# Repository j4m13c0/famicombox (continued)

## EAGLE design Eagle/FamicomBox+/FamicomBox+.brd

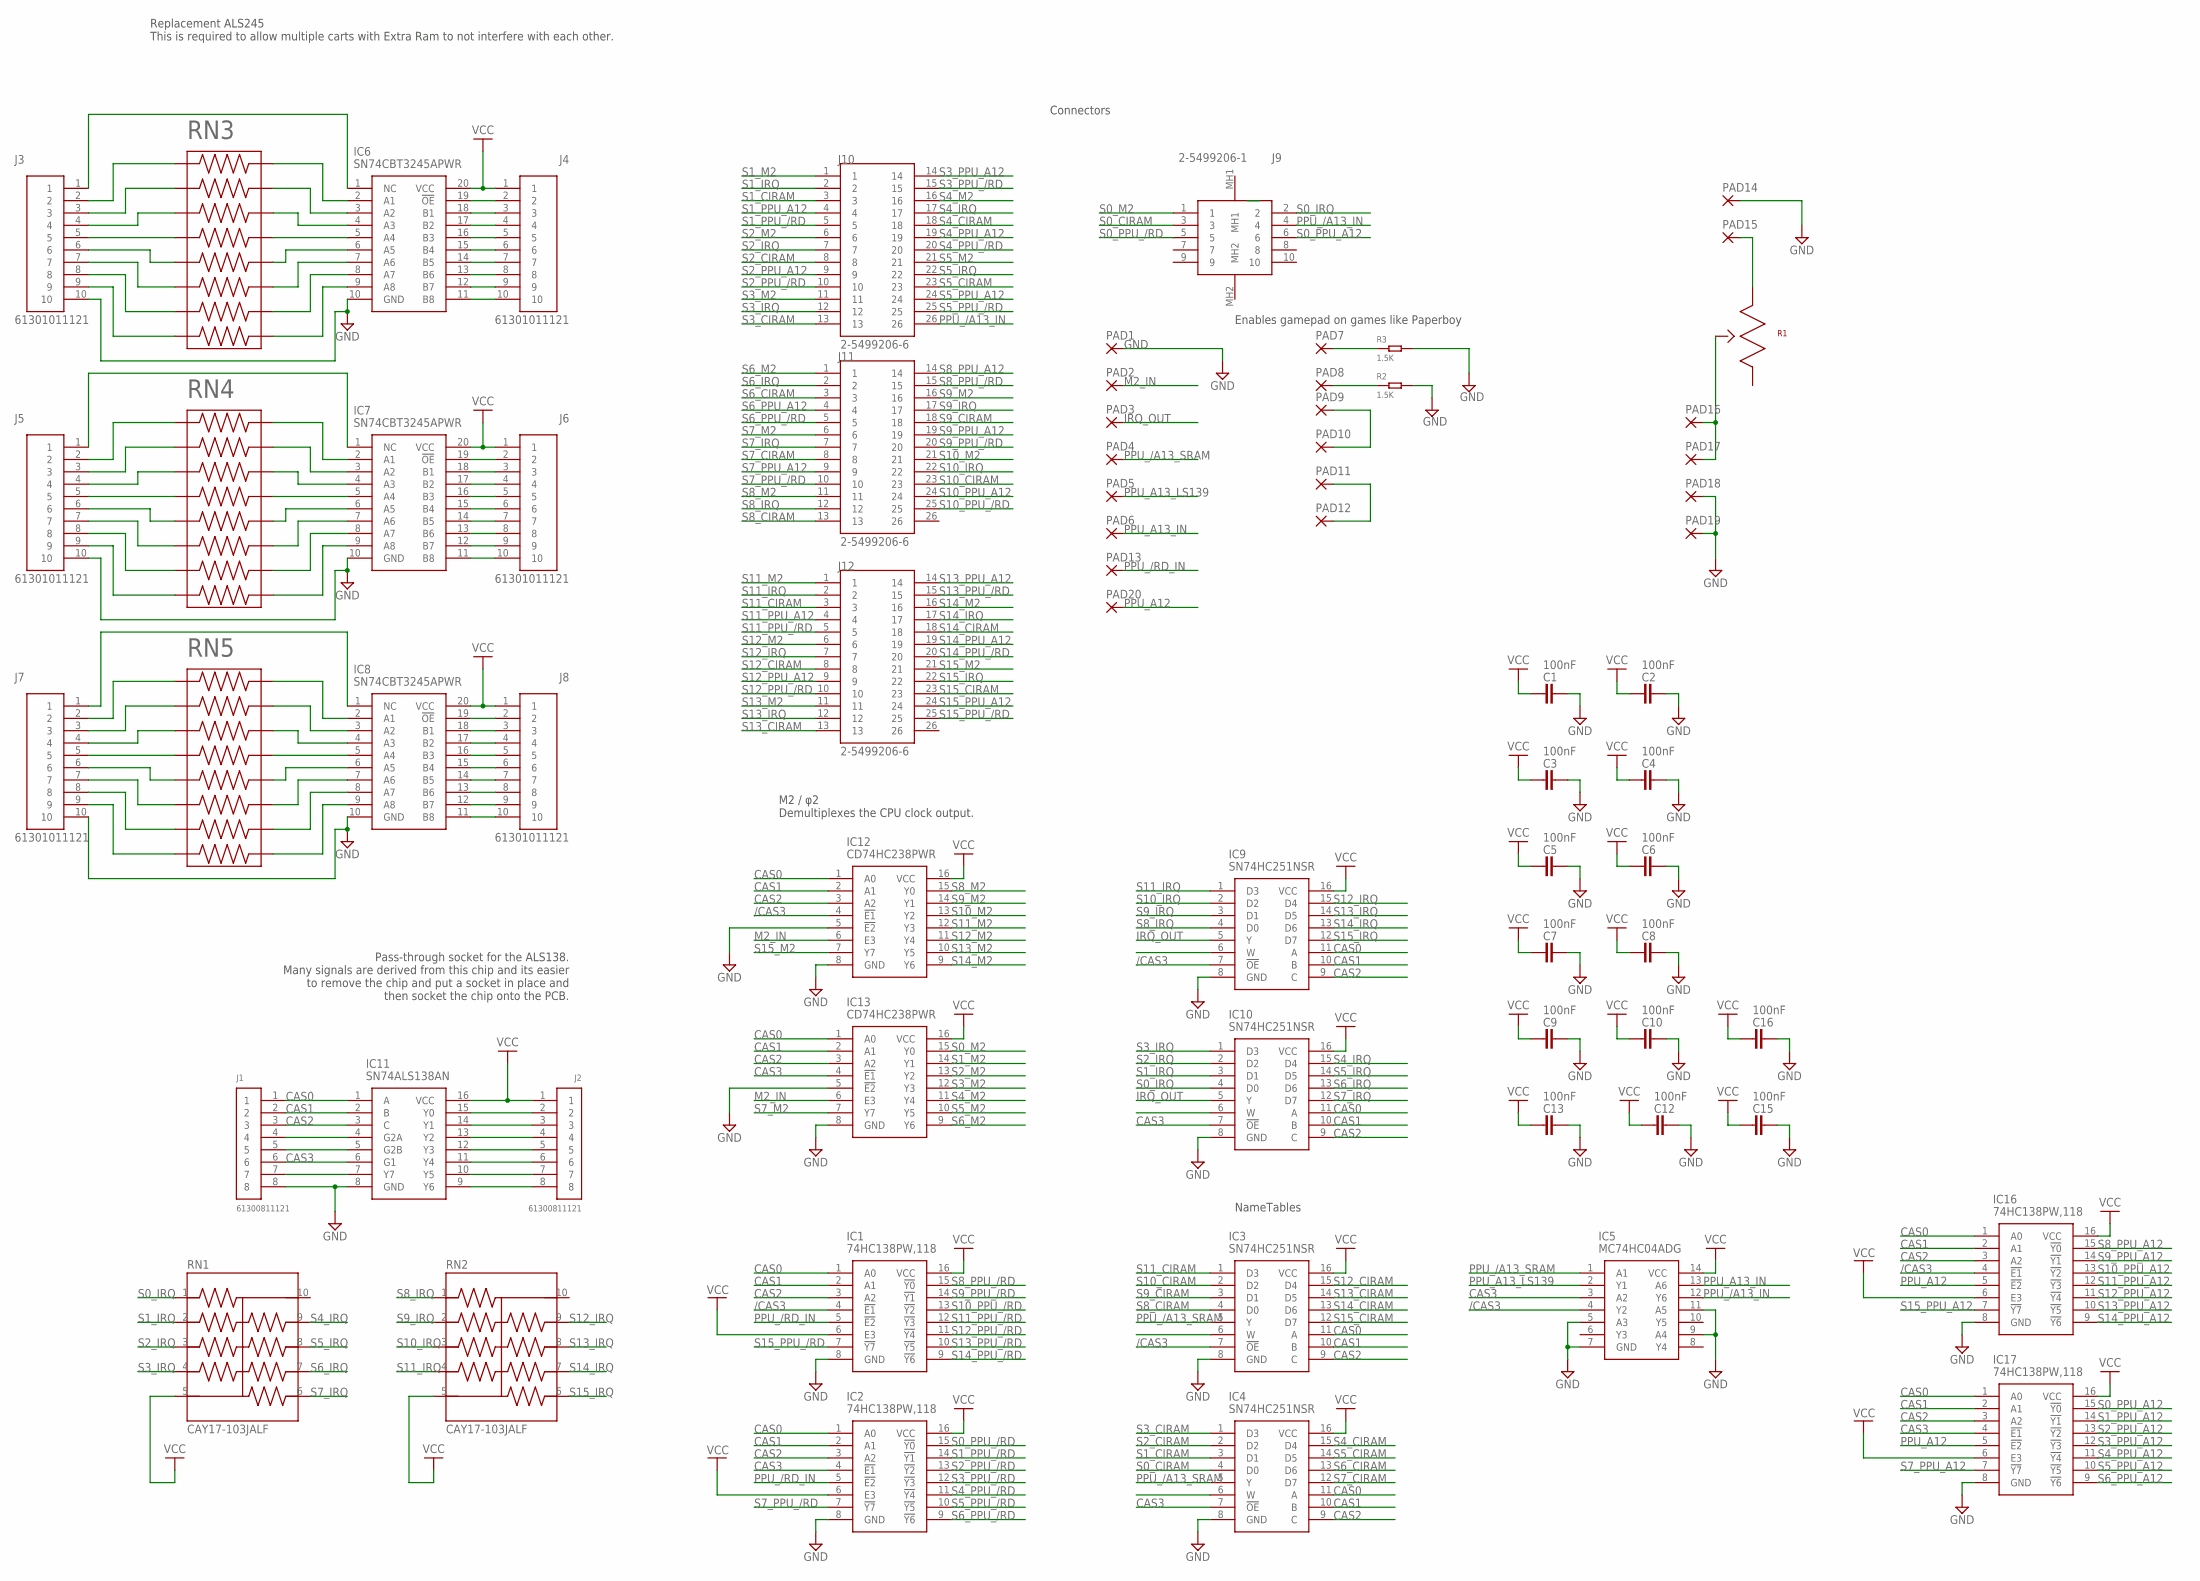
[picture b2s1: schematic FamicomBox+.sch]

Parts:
C1, C2, C3, C4, C5, C6, C7, C8, C9, C10, C12, C13, C15, C16: 100nF; CAPC1608X85
IC1, IC2, IC16, IC17: 74HC138PW,118; SOP65P640X110-16N
IC3, IC4, IC9, IC10: SN74HC251NSR; SOIC127P780X200-16N
IC5: MC74HC04ADG; SOIC127P600X175-14N
IC6, IC7, IC8: SN74CBT3245APWR; SOP65P640X120-20N
IC11: SN74ALS138AN; DIP254P762X508-16
IC12, IC13: CD74HC238PWR; SOP65P640X120-16N
J1, J2: 61300811121
J3, J4, J5, J6, J7, J8: 61301011121
J9: 2-5499206-1; 254992061
J10, J11, J12: 2-5499206-6; TE_2-5499206-6
PAD1, PAD2, PAD3, PAD4, PAD5, PAD6, PAD7, PAD8, PAD9, PAD10, PAD11, PAD12, PAD13, PAD14, PAD15, PAD16, PAD17, PAD18, PAD19, PAD20: WIREPAD2,54/1,0; 2,54/1,0
R1: PTV09A-4020F-A504; PTV09
R2, R3: 1.5K; R0603
RN1, RN2: CAY17-103JALF; RESCAXS64P320X160X60-10N
RN3, RN4, RN5: 4816P-1-562LF; SOIC127P762X240-16N

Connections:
/CAS3: IC1.4 (!E1), IC3.7 (!OE), IC5.4 (Y2), IC9.7 (!OE), IC12.4 (!E1), IC16.4 (!E1)
CAS0: IC1.1 (A0), IC2.1 (A0), IC3.11 (A), IC4.11 (A), IC9.11 (A), IC10.11 (A), IC11.1 (A), IC12.1 (A0), IC13.1 (A0), IC16.1 (A0), IC17.1 (A0), J1.1
CAS1: IC1.2 (A1), IC2.2 (A1), IC3.10 (B), IC4.10 (B), IC9.10 (B), IC10.10 (B), IC11.2 (B), IC12.2 (A1), IC13.2 (A1), IC16.2 (A1), IC17.2 (A1), J1.2
CAS2: IC1.3 (A2), IC2.3 (A2), IC3.9 (C), IC4.9 (C), IC9.9 (C), IC10.9 (C), IC11.3 (C), IC12.3 (A2), IC13.3 (A2), IC16.3 (A2), IC17.3 (A2), J1.3
CAS3: IC2.4 (!E1), IC4.7 (!OE), IC5.3 (A2), IC10.7 (!OE), IC11.6 (G1), IC13.4 (!E1), IC17.4 (!E1), J1.6
GND: C1.1, C2.1, C3.1, C4.1, C5.1, C6.1, C7.1, C8.1, C9.1, C10.1, C12.1, C13.1, C15.1, C16.1, IC1.8 (GND), IC2.8 (GND), IC3.8 (GND), IC4.8 (GND), IC5.5 (A3), IC5.7 (GND), IC5.9 (A4), IC5.11 (A5), IC6.10 (GND), IC7.10 (GND), IC8.10 (GND), IC9.8 (GND), IC10.8 (GND), IC11.8 (GND), IC12.5 (!E2), IC12.8 (GND), IC13.5 (!E2), IC13.8 (GND), IC16.8 (GND), IC17.8 (GND), J1.8, J3.10, J5.10, J7.10, PAD1.1, PAD14.1, PAD18.1, PAD19.1, R2.2, R3.2
IRQ_OUT: IC9.5 (Y), IC10.5 (Y), PAD3.1
M2_IN: IC12.6 (E3), IC13.6 (E3), PAD2.1
unnamed: IC6.2 (A1), RN3.16
unnamed: IC6.3 (A2), RN3.15
unnamed: IC6.4 (A3), RN3.14
unnamed: IC6.5 (A4), RN3.13
unnamed: IC6.6 (A5), RN3.12
unnamed: IC6.7 (A6), RN3.11
unnamed: IC6.8 (A7), RN3.10
unnamed: IC6.9 (A8), RN3.9
unnamed: J3.2, RN3.1
unnamed: J3.3, RN3.2
unnamed: IC6.11 (B8), J4.10
unnamed: IC6.12 (B7), J4.9
unnamed: IC6.13 (B6), J4.8
unnamed: IC6.14 (B5), J4.7
unnamed: IC6.15 (B4), J4.6
unnamed: IC6.16 (B3), J4.5
unnamed: IC6.17 (B2), J4.4
unnamed: IC6.18 (B1), J4.3
unnamed: IC6.19 (!OE), J4.2
unnamed: J3.4, RN3.3
unnamed: J3.5, RN3.4
unnamed: J3.6, RN3.5
unnamed: J3.7, RN3.6
unnamed: J3.8, RN3.7
unnamed: J3.9, RN3.8
unnamed: IC6.1 (NC), J3.1
unnamed: J7.2, RN5.1
unnamed: IC7.11 (B8), J6.10
unnamed: IC7.12 (B7), J6.9
unnamed: IC7.13 (B6), J6.8
unnamed: IC7.14 (B5), J6.7
unnamed: IC7.15 (B4), J6.6
unnamed: IC7.16 (B3), J6.5
unnamed: IC7.17 (B2), J6.4
unnamed: IC7.18 (B1), J6.3
unnamed: IC7.19 (!OE), J6.2
unnamed: IC8.19 (!OE), J8.2
unnamed: IC8.18 (B1), J8.3
unnamed: IC8.17 (B2), J8.4
unnamed: IC8.16 (B3), J8.5
unnamed: IC8.15 (B4), J8.6
unnamed: IC8.14 (B5), J8.7
unnamed: IC8.13 (B6), J8.8
unnamed: IC8.12 (B7), J8.9
unnamed: IC8.11 (B8), J8.10
unnamed: IC7.5 (A4), RN4.13
unnamed: J5.5, RN4.4
unnamed: J5.2, RN4.1
unnamed: J5.3, RN4.2
unnamed: J5.4, RN4.3
unnamed: J5.6, RN4.5
unnamed: J5.7, RN4.6
unnamed: J5.8, RN4.7
unnamed: J5.9, RN4.8
unnamed: IC11.15 (Y0), J2.2
unnamed: IC11.14 (Y1), J2.3
unnamed: IC11.13 (Y2), J2.4
unnamed: IC11.12 (Y3), J2.5
unnamed: IC11.11 (Y4), J2.6
unnamed: IC11.10 (Y5), J2.7
unnamed: IC11.9 (Y6), J2.8
unnamed: IC11.4 (G2A), J1.4
unnamed: PAD9.1, PAD10.1
unnamed: PAD11.1, PAD12.1
unnamed: IC7.4 (A3), RN4.14
unnamed: IC11.5 (G2B), J1.5
unnamed: IC7.3 (A2), RN4.15
unnamed: IC11.7 (Y7), J1.7
unnamed: IC7.2 (A1), RN4.16
unnamed: IC7.1 (NC), J5.1
unnamed: IC7.6 (A5), RN4.12
unnamed: IC7.7 (A6), RN4.11
unnamed: IC7.8 (A7), RN4.10
unnamed: IC7.9 (A8), RN4.9
unnamed: J7.3, RN5.2
unnamed: J7.5, RN5.4
unnamed: IC8.5 (A4), RN5.13
unnamed: IC8.4 (A3), RN5.14
unnamed: IC8.3 (A2), RN5.15
unnamed: IC8.2 (A1), RN5.16
unnamed: IC8.6 (A5), RN5.12
unnamed: IC8.7 (A6), RN5.11
unnamed: IC8.8 (A7), RN5.10
unnamed: IC8.9 (A8), RN5.9
unnamed: IC8.1 (NC), J7.1
unnamed: J7.4, RN5.3
unnamed: J7.6, RN5.5
unnamed: J7.7, RN5.6
unnamed: J7.8, RN5.7
unnamed: J7.9, RN5.8
unnamed: PAD15.1, R1.1
unnamed: PAD16.1, PAD17.1, R1.2
unnamed: PAD8.1, R2.1
unnamed: PAD7.1, R3.1
PPU_/A13_IN: IC5.12 (Y6), J9.4, J10.26
PPU_/A13_SRAM: IC3.5 (Y), IC4.5 (Y), IC5.1 (A1), PAD4.1
PPU_/RD_IN: IC1.5 (!E2), IC2.5 (!E2), PAD13.1
PPU_A12: IC16.5 (!E2), IC17.5 (!E2), PAD20.1
PPU_A13_IN: IC5.13 (A6), PAD6.1
PPU_A13_LS139: IC5.2 (Y1), PAD5.1
S0_CIRAM: IC4.4 (D0), J9.3
S0_IRQ: IC10.4 (D0), J9.2, RN1.1
S0_M2: IC13.15 (Y0), J9.1
S0_PPU_/RD: IC2.15 (!Y0), J9.5
S0_PPU_A12: IC17.15 (!Y0), J9.6
S1_CIRAM: IC4.3 (D1), J10.3
S1_IRQ: IC10.3 (D1), J10.2, RN1.2
S1_M2: IC13.14 (Y1), J10.1
S1_PPU_/RD: IC2.14 (!Y1), J10.5
S1_PPU_A12: IC17.14 (!Y1), J10.4
S2_CIRAM: IC4.2 (D2), J10.8
S2_IRQ: IC10.2 (D2), J10.7, RN1.3
S2_M2: IC13.13 (Y2), J10.6
S2_PPU_/RD: IC2.13 (!Y2), J10.10
S2_PPU_A12: IC17.13 (!Y2), J10.9
S3_CIRAM: IC4.1 (D3), J10.13
S3_IRQ: IC10.1 (D3), J10.12, RN1.4
S3_M2: IC13.12 (Y3), J10.11
S3_PPU_/RD: IC2.12 (!Y3), J10.15
S3_PPU_A12: IC17.12 (!Y3), J10.14
S4_CIRAM: IC4.15 (D4), J10.18
S4_IRQ: IC10.15 (D4), J10.17, RN1.9
S4_M2: IC13.11 (Y4), J10.16
S4_PPU_/RD: IC2.11 (!Y4), J10.20
S4_PPU_A12: IC17.11 (!Y4), J10.19
S5_CIRAM: IC4.14 (D5), J10.23
S5_IRQ: IC10.14 (D5), J10.22, RN1.8
S5_M2: IC13.10 (Y5), J10.21
S5_PPU_/RD: IC2.10 (!Y5), J10.25
S5_PPU_A12: IC17.10 (!Y5), J10.24
S6_CIRAM: IC4.13 (D6), J11.3
S6_IRQ: IC10.13 (D6), J11.2, RN1.7
S6_M2: IC13.9 (Y6), J11.1
S6_PPU_/RD: IC2.9 (!Y6), J11.5
S6_PPU_A12: IC17.9 (!Y6), J11.4
S7_CIRAM: IC4.12 (D7), J11.8
S7_IRQ: IC10.12 (D7), J11.7, RN1.6
S7_M2: IC13.7 (Y7), J11.6
S7_PPU_/RD: IC2.7 (!Y7), J11.10
S7_PPU_A12: IC17.7 (!Y7), J11.9
S8_CIRAM: IC3.4 (D0), J11.13
S8_IRQ: IC9.4 (D0), J11.12, RN2.1
S8_M2: IC12.15 (Y0), J11.11
S8_PPU_/RD: IC1.15 (!Y0), J11.15
S8_PPU_A12: IC16.15 (!Y0), J11.14
S9_CIRAM: IC3.3 (D1), J11.18
S9_IRQ: IC9.3 (D1), J11.17, RN2.2
S9_M2: IC12.14 (Y1), J11.16
S9_PPU_/RD: IC1.14 (!Y1), J11.20
S9_PPU_A12: IC16.14 (!Y1), J11.19
S10_CIRAM: IC3.2 (D2), J11.23
S10_IRQ: IC9.2 (D2), J11.22, RN2.3
S10_M2: IC12.13 (Y2), J11.21
S10_PPU_/RD: IC1.13 (!Y2), J11.25
S10_PPU_A12: IC16.13 (!Y2), J11.24
S11_CIRAM: IC3.1 (D3), J12.3
S11_IRQ: IC9.1 (D3), J12.2, RN2.4
S11_M2: IC12.12 (Y3), J12.1
S11_PPU_/RD: IC1.12 (!Y3), J12.5
S11_PPU_A12: IC16.12 (!Y3), J12.4
S12_CIRAM: IC3.15 (D4), J12.8
S12_IRQ: IC9.15 (D4), J12.7, RN2.9
S12_M2: IC12.11 (Y4), J12.6
S12_PPU_/RD: IC1.11 (!Y4), J12.10
S12_PPU_A12: IC16.11 (!Y4), J12.9
S13_CIRAM: IC3.14 (D5), J12.13
S13_IRQ: IC9.14 (D5), J12.12, RN2.8
S13_M2: IC12.10 (Y5), J12.11
S13_PPU_/RD: IC1.10 (!Y5), J12.15
S13_PPU_A12: IC16.10 (!Y5), J12.14
S14_CIRAM: IC3.13 (D6), J12.18
S14_IRQ: IC9.13 (D6), J12.17, RN2.7
S14_M2: IC12.9 (Y6), J12.16
S14_PPU_/RD: IC1.9 (!Y6), J12.20
S14_PPU_A12: IC16.9 (!Y6), J12.19
S15_CIRAM: IC3.12 (D7), J12.23
S15_IRQ: IC9.12 (D7), J12.22, RN2.6
S15_M2: IC12.7 (Y7), J12.21
S15_PPU_/RD: IC1.7 (!Y7), J12.25
S15_PPU_A12: IC16.7 (!Y7), J12.24
VCC: C1.2, C2.2, C3.2, C4.2, C5.2, C6.2, C7.2, C8.2, C9.2, C10.2, C12.2, C13.2, C15.2, C16.2, IC1.6 (E3), IC1.16 (VCC), IC2.6 (E3), IC2.16 (VCC), IC3.16 (VCC), IC4.16 (VCC), IC5.14 (VCC), IC6.20 (VCC), IC7.20 (VCC), IC8.20 (VCC), IC9.16 (VCC), IC10.16 (VCC), IC11.16 (VCC), IC12.16 (VCC), IC13.16 (VCC), IC16.6 (E3), IC16.16 (VCC), IC17.6 (E3), IC17.16 (VCC), J2.1, J4.1, J6.1, J8.1, RN1.5, RN2.5

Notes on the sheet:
Replacement ALS245 This is required to allow multiple carts with Extra Ram to not interfere with each other.
Pass-through socket for the ALS138. Many signals are derived from this chip and its easier to remove the chip and put a socket in place and then socket the chip onto the PCB.
Connectors
M2 / φ2 Demultiplexes the CPU clock output.
Enables gamepad on games like Paperboy
NameTables

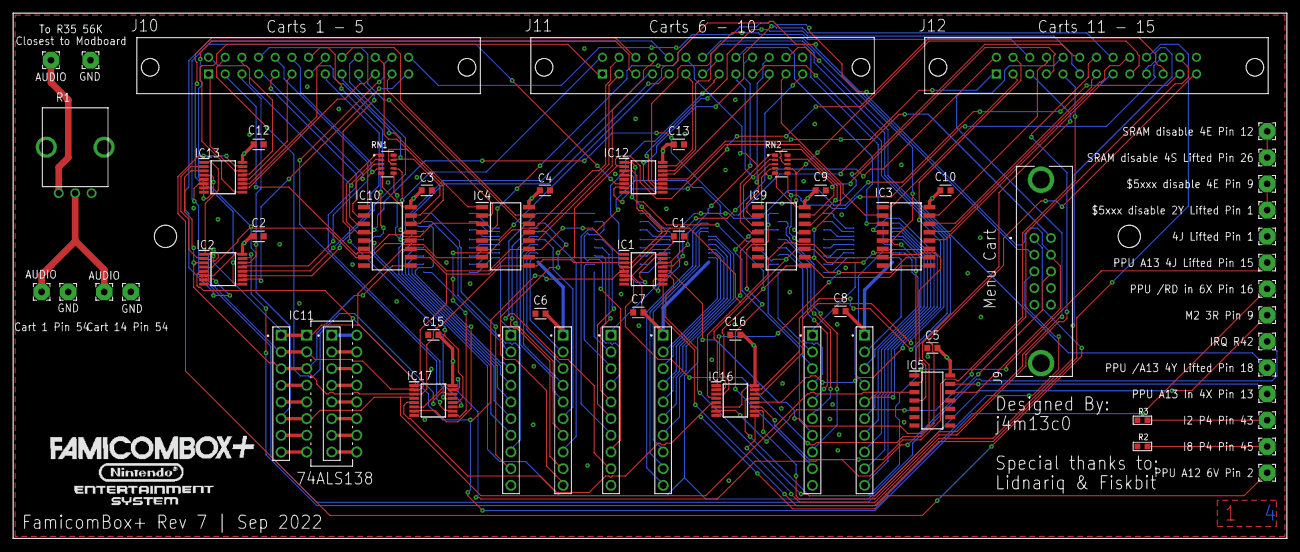
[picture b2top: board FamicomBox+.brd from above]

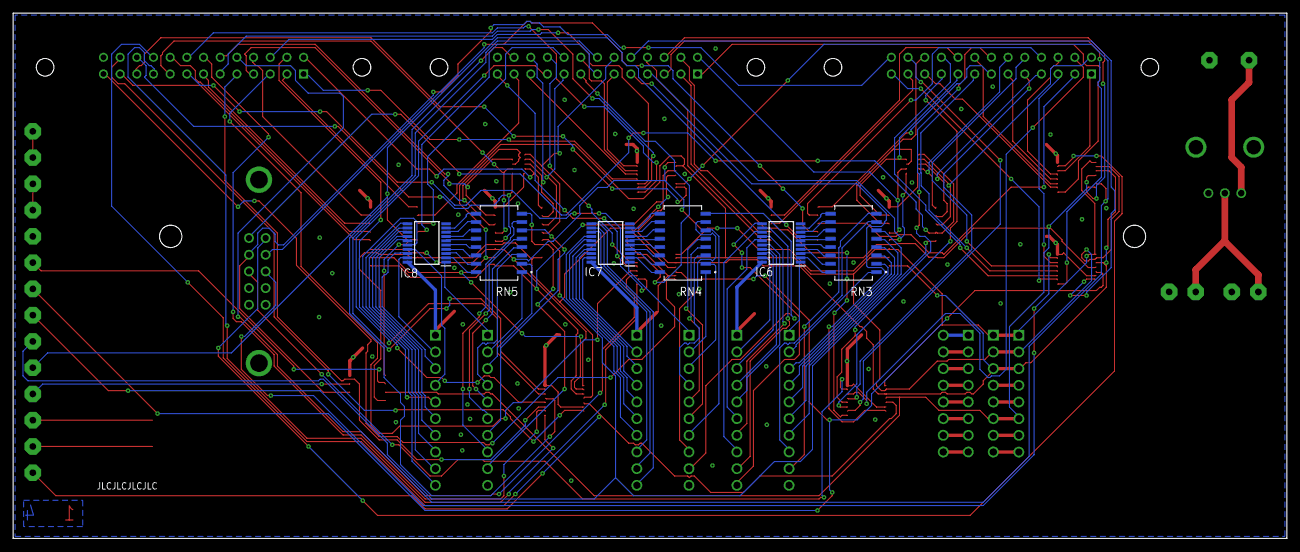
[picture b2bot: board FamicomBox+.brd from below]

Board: 4 copper layers, 194.0 x 80.0 mm, 69 parts (6 on the bottom side), 189 nets.

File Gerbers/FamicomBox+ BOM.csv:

Part,Value,Mouser PN
C1,100nF,581-06035C104KAT2A
C2,100nF,581-06035C104KAT2A
C3,100nF,581-06035C104KAT2A
C4,100nF,581-06035C104KAT2A
C5,100nF,581-06035C104KAT2A
C6,100nF,581-06035C104KAT2A
C7,100nF,581-06035C104KAT2A
C8,100nF,581-06035C104KAT2A
C9,100nF,581-06035C104KAT2A
C10,100nF,581-06035C104KAT2A
C12,100nF,581-06035C104KAT2A
C13,100nF,581-06035C104KAT2A
C15,100nF,581-06035C104KAT2A
C16,100nF,581-06035C104KAT2A
IC1,"74HC138PW,118",771-74HC138PW-T
IC2,"74HC138PW,118",771-74HC138PW-T
IC3,SN74HC251NSR,595-SN74HC251NSR
IC4,SN74HC251NSR,595-SN74HC251NSR
IC5,MC74HC04ADG,863-MC74HC04ADG
IC6,SN74CBT3245APWR,595-SN74CBT3245APWR
IC7,SN74CBT3245APWR,595-SN74CBT3245APWR
IC8,SN74CBT3245APWR,595-SN74CBT3245APWR
IC9,SN74HC251NSR,595-SN74HC251NSR
IC10,SN74HC251NSR,595-SN74HC251NSR
IC11,SN74ALS138AN,595-SN74ALS138AN
IC12,CD74HC238PWR,595-CD74HC238PWR
IC13,CD74HC238PWR,595-CD74HC238PWR
IC16,"74HC138PW,118",771-74HC138PW-T
IC17,"74HC138PW,118",771-74HC138PW-T
J1,Pin Strip,
J2,Pin Strip,
J3,Pin Strip,
J4,Pin Strip,
J5,Pin Strip,
J6,Pin Strip,
J7,Pin Strip,
J8,Pin Strip,
J9,2-5499206-1,571-2-5499206-1
J9 Cable Conn,1658527-4,571-1658527-4
J10,2-5499206-6,571-2-5499206-6
J10 Cable Conn,1-1658527-0,571-1-1658527-0
J11,2-5499206-6,571-2-5499206-6
J11 Cable Conn,1-1658527-0,571-1-1658527-0
J12,2-5499206-6,571-2-5499206-6
J12 Cable Conn,1-1658527-0,571-1-1658527-0
R1,PTV09A-4020F-A504,652-PTV09A-4020FA504
R2,1.5K,CR0603-FX-1501ELF
R3,1.5K,CR0603-FX-1501ELF
RN1,CAY17-103JALF,652-CAY17-103JALF
RN2,CAY17-103JALF,652-CAY17-103JALF
RN3,4816P-T01-101LF,652-4816P-T1LF-100
RN4,4816P-T01-101LF,652-4816P-T1LF-100
RN5,4816P-T01-101LF,652-4816P-T1LF-100

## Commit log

2022-09-22 Initial commit
    Initial commit
2022-09-22 Fixed Layout
2022-09-22 Added BOM
